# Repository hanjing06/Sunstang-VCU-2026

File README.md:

# Sunstang VCU 2026  
Vehicle Control Unit PCB for Western Sunstang

---

## Overview

The **Sunstang VCU 2026** is a custom-designed Vehicle Control Unit PCB developed in **KiCad v6+**.

The board integrates driver inputs, high-voltage enable logic, lighting control, safety interlocks, and vehicle state management into a centralized low-voltage control system.

The system is built around the **STM32 Nucleo-F302R8** development board (ARM Cortex-M4, 3.3V logic).

This PCB acts as the hardware interface between the microcontroller and the vehicle’s 12V automotive systems.

---

## System Architecture

The VCU operates across two voltage domains:

| Domain | Voltage | Description |
|--------|---------|-------------|
| Logic Domain | 3.3V | STM32 microcontroller logic |
| Automotive LV Domain | 12V | Switches, contactors, lighting, HV control |

Signal conditioning ensures safe interfacing between 12V automotive signals and 3.3V MCU GPIO/ADC inputs.

---

### System Integration Diagram

The diagram below shows the high-level integration of:

- STM32 Nucleo-F302R8 (3.3V logic domain)
- 12V automotive domain subsystems
- Pre-charge & contactor control
- Driver interface
- Lighting systems
- BMS interface

---

## Microcontroller

**Board:** STM32 Nucleo-F302R8  
**Core:** ARM Cortex-M4  
**Logic Voltage:** 3.3V  

Primary functions:
- ADC acquisition (accelerator and brake pedals)
- Digital input processing (switches and selectors)
- Digital output control (contactors, LEDs, lighting)
- Vehicle state logic (ready mode, charge mode, HV enable)

Documentation:  
https://www.st.com/en/evaluation-tools/nucleo-f302r8.html

---

## Functional Responsibilities

The VCU manages the following subsystems:

### 1. Power & HV Control
- LV switch interface (12V)
- HV switch interface (12V)
- Pre-charge button input
- Pre-charge contactor feedback
- Main contactor feedback
- HV active indication
- BMS interface signals

### 2. Driver Inputs
- Accelerator pedal (ADC input)
- Brake pedal (ADC/digital input)
- Brake light trigger output

### 3. Mode Control
- Ready mode switch
- Charge mode switch
- Mode select (SPDT)
- Gear selector (SPST)

### 4. Lighting Control
- Brake lights
- Daytime running lights (DRL)
- Left turn signal
- Right turn signal
- Hazard (latching)
- Rear signal outputs

### 5. Safety Inputs
- HV active confirmation
- Thermal shutdown input (redundancy planned)
- Pre-charge verification before main contactor closure

---

## Startup Sequence (Simplified)

1. LV switch enabled  
2. HV switch engaged  
3. Pre-charge initiated  
4. Pre-charge confirmed  
5. Main contactor closed  
6. HV active verified  
7. Ready mode enabled  
8. Vehicle operational  

---

## Electrical Characteristics

| Parameter | Value |
|------------|--------|
| Automotive LV Input | 12V DC |
| MCU Logic Voltage | 3.3V |
| Microcontroller | STM32F302R8 |
| Design Tool | KiCad v6+ |

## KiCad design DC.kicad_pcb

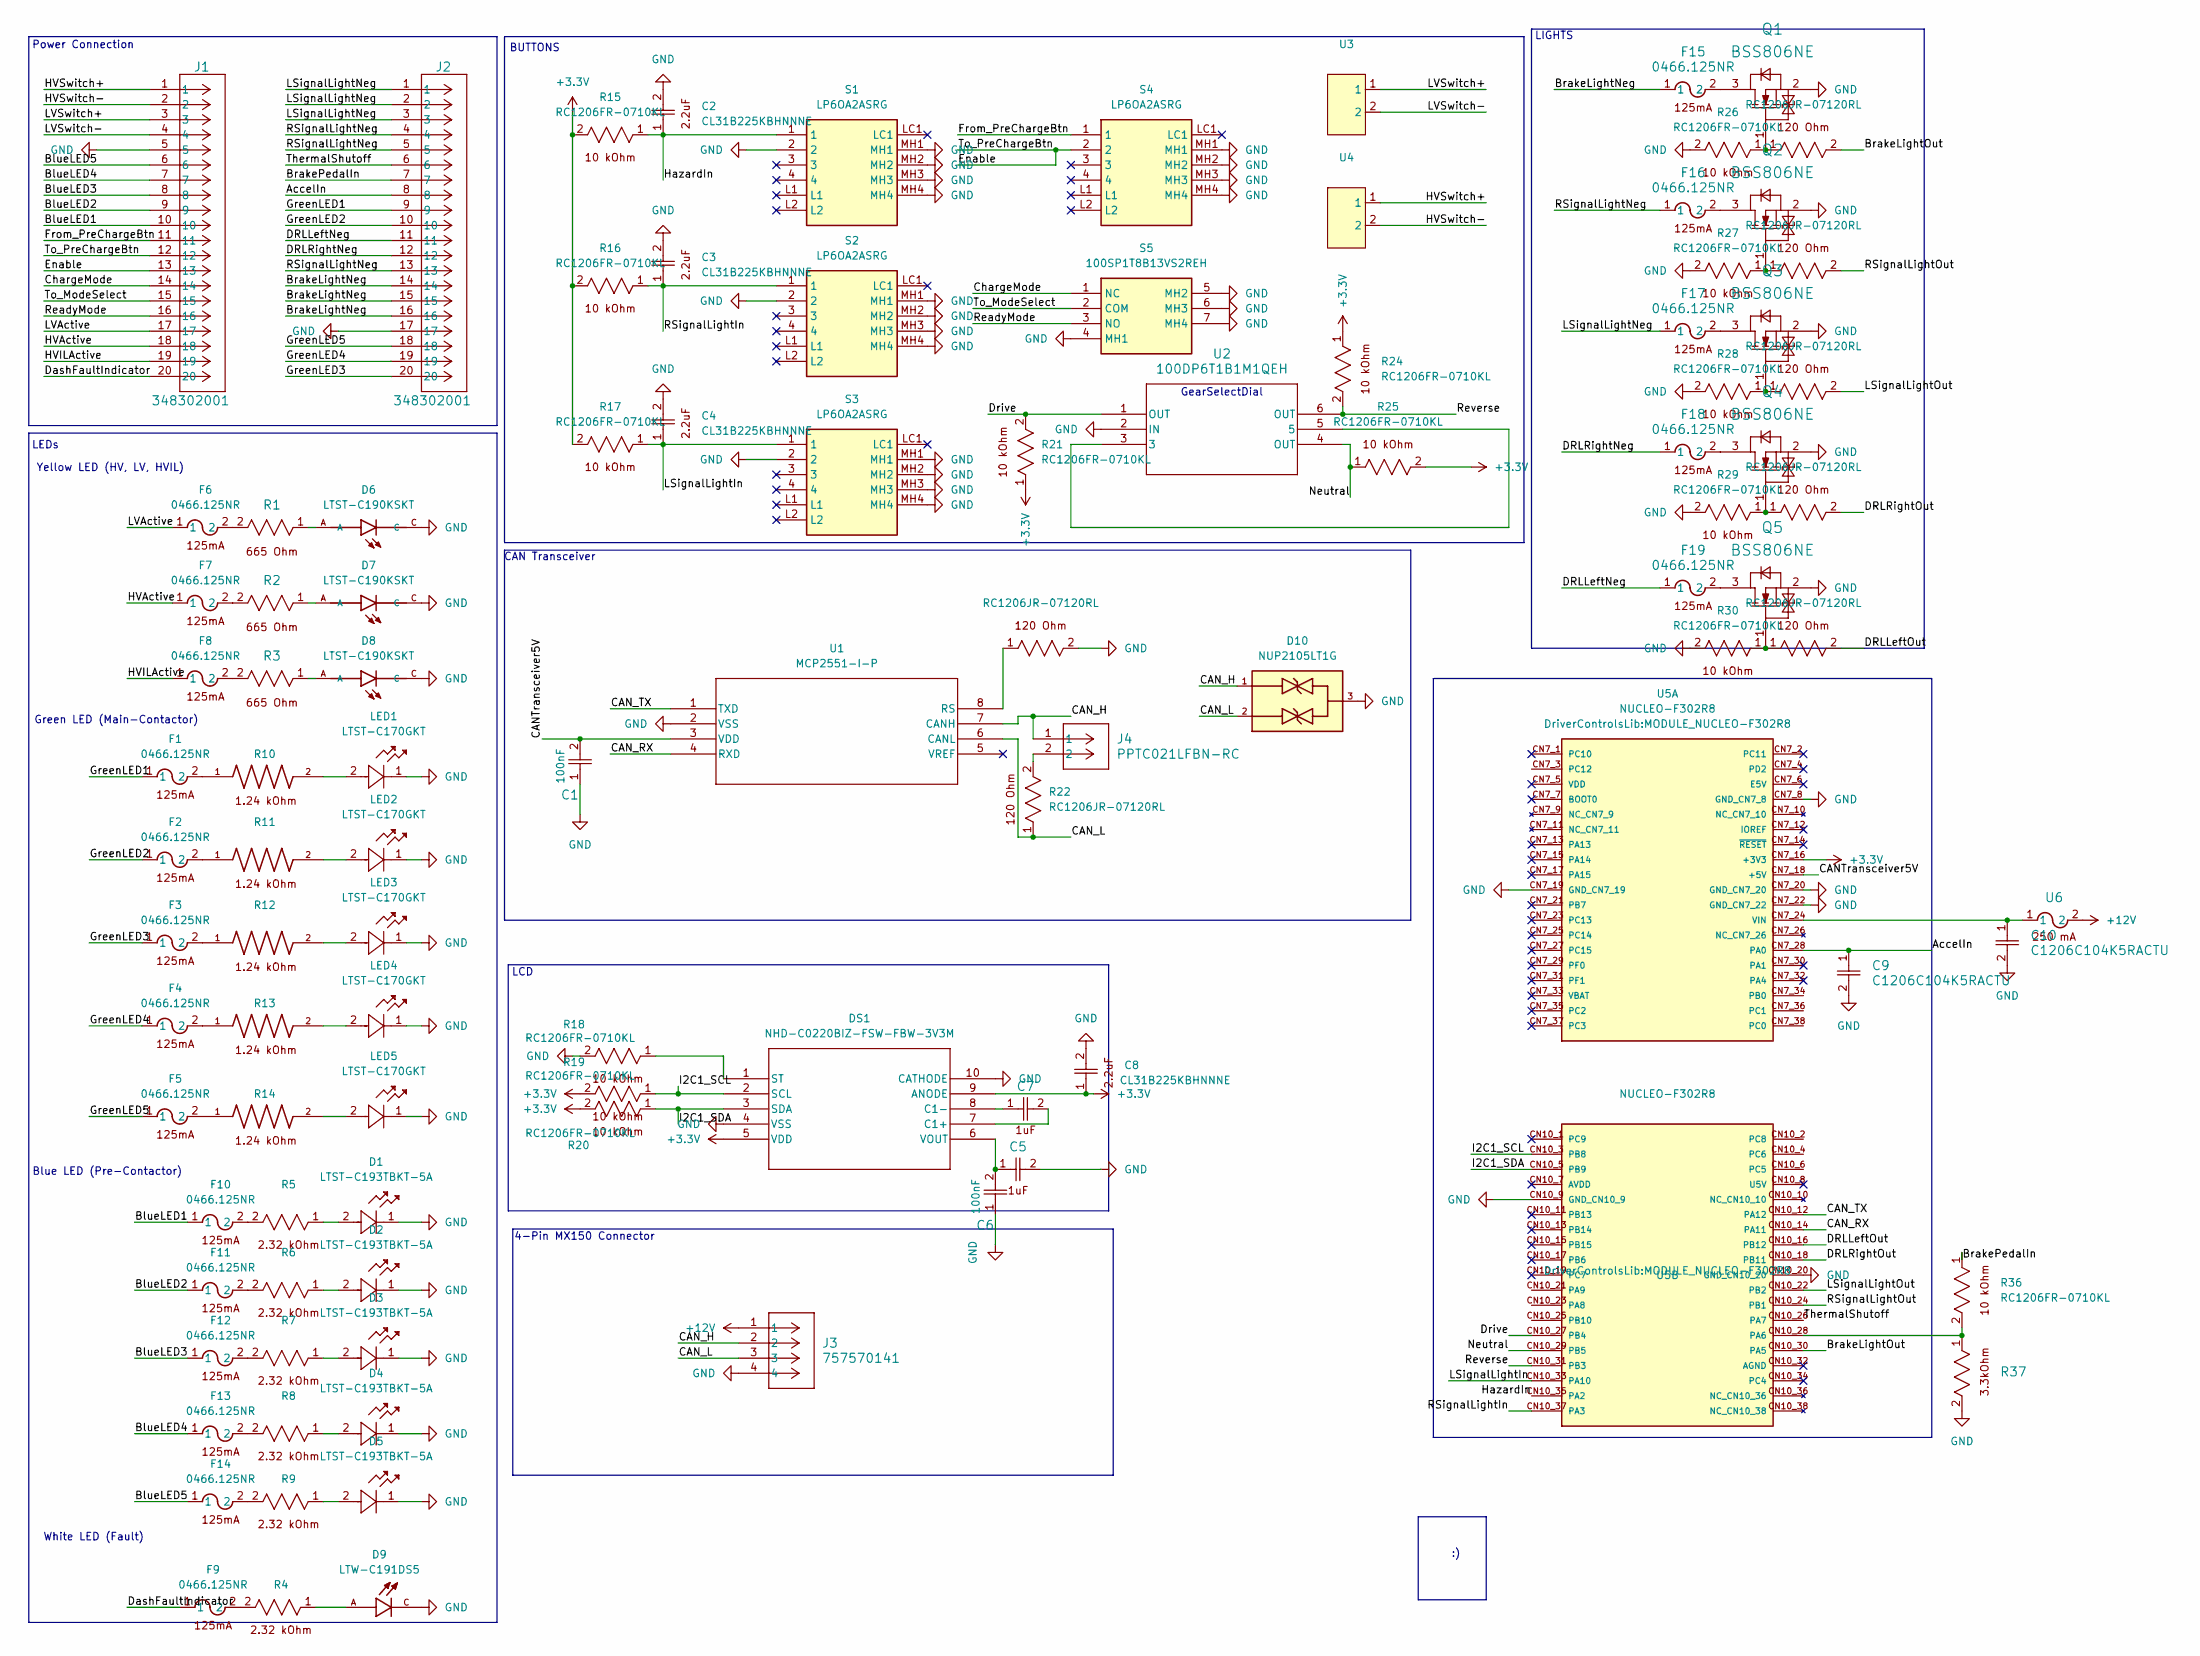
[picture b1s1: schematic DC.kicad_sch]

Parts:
C1, C6, C9, C10: C1206C104K5RACTU; CAPC340180_88N_KEM
C2, C3, C4, C8: CL31B225KBHNNNE; CAP_CL31_SAM
C5, C7: CL31B105KAHNNNE; CAP_CL31_SAM
D1, D2, D3, D4, D5: LTST-C193TBKT-5A; LED_LTST-C_LTO
D6, D7, D8: LTST-C190KSKT; LEDM1608X80
D9: LTW-C191DS5; LEDC1608X65N
D10: NUP2105LT1G; SOT95P237X111-3N; PARTREV 10
DS1: NHD-C0220BIZ-FSW-FBW-3V3M; NHD-C0220BIZ-FSW-FBW-3V3M_NDI; PARTREV 1.0
F1, F2, F3, F4, F5, F6, F7, F8, F9, F10, F11, F12, F13, F14: 0466.125NR; 0466Series_LTF; Mouser Part Number 576-0466.125NR
F15, F16, F17, F18, F19: 0466.125NR; 0466Series_LTF
J1, J2: 348302001; CONN_SD-34829-001_20_ST_MOL
J3: 757570141; CONN_SD-75757-010_1X4_F11p20_MOL
J4: PPTC021LFBN-RC; CONN2_LFBN-RC_SUL
LED1, LED2, LED3, LED4, LED5: LTST-C170GKT; LED_LTST-C170GKT_LTO
Q1, Q2, Q3, Q4, Q5: BSS806NE; SOT95P240X110-3N-1-V1
R1, R2, R3: RC1206FR-07665RL; RC1206N_YAG
R4, R5, R6, R7, R8, R9: RC1206FR-072K32L; RC1206N_YAG
R10, R11, R12, R13, R14: RC1206FR-071K24L; RESC3116X65N
R15, R16, R17, R18, R19, R20, R21, R24, R25, R26, R27, R28, R29, R30, R36: RC1206FR-0710KL; RC1206N_YAG
R22, R23, R31, R32, R33, R34, R35: RC1206JR-07120RL; RC1206N_YAG
R37: RC1206FR-073K3L; RC1206N_YAG
S1, S2, S3, S4: LP6OA2ASRG; Mouser Part Number 612-LP6OA2ASRG
S5: 100SP1T8B13VS2REH; Manufacturer_Part_Number 100SP1T8B13VS2REH
U1: MCP2551-I-P; PDIP8_300MC_MCH
U2: 100DP6T1B1M1QEH; TO_1M1QEH_EWI
U3: LV_Switch
U4: HV_Switch
U5: NUCLEO-F302R8; MODULE_NUCLEO-F302R8; PARTREV 17
U6: C1F 250; C1_BEL

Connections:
+3.3V: C8.1, DS1.5 (VDD), DS1.9 (ANODE), R15.2, R16.2, R17.2, R19.2, R20.2, R21.1, R24.1, R25.2, U5.CN7_16 (+3V3); also elsewhere on the board
+12V: J3.1, U6.2
/AccelIn: C9.1, J2.8, U5.CN7_28 (PA0)
/BlueLED1: F10.1, J1.10
/BlueLED2: F11.1, J1.9
/BlueLED3: F12.1, J1.8
/BlueLED4: F13.1, J1.7
/BlueLED5: F14.1, J1.6
/BrakeLightNeg: F15.1, J2.14, J2.15, J2.16
/BrakeLightOut: R31.2, U5.CN10_30 (PA5)
/BrakePedalIn: J2.7, R36.1
/CANTransceiver5V: C1.2, U1.3 (VDD), U5.CN7_18 (+5V)
/CAN_H: D10.1, J3.2, J4.1, U1.7 (CANH)
/CAN_L: D10.2, J3.3, R22.1, U1.6 (CANL)
/CAN_RX: U1.4 (RXD), U5.CN10_14 (PA11)
/CAN_TX: U1.1 (TXD), U5.CN10_12 (PA12)
/ChargeMode: J1.14, S5.1 (NC)
/DRLLeftNeg: F19.1, J2.11
/DRLLeftOut: R35.2, U5.CN10_16 (PB12)
/DRLRightNeg: F18.1, J2.12
/DRLRightOut: R34.2, U5.CN10_18 (PB11)
/DashFaultIndicator: F9.1, J1.20
/Drive: R21.2, U2.1 (OUT), U5.CN10_27 (PB4)
/Enable: J1.12, J1.13, S4.2
/From_PreChargeBtn: J1.11, S4.1
/GreenLED1: F1.1, J2.9
/GreenLED2: F2.1, J2.10
/GreenLED3: F3.1, J2.20
/GreenLED4: F4.1, J2.19
/GreenLED5: F5.1, J2.18
/HVActive: F7.1, J1.18
/HVILActive: F8.1, J1.19
/HVSwitch+: J1.1, U4.1
/HVSwitch-: J1.2, U4.2
/HazardIn: C2.1, R15.1, S1.1, U5.CN10_35 (PA2)
/I2C1_SCL: DS1.2 (SCL), R19.1, U5.CN10_3 (PB8)
/I2C1_SDA: DS1.3 (SDA), R20.1, U5.CN10_5 (PB9)
/LSignalLightIn: C4.1, R17.1, S3.1, U5.CN10_33 (PA10)
/LSignalLightNeg: F17.1, J2.1, J2.2, J2.3
/LSignalLightOut: R33.2, U5.CN10_22 (PB2)
/LVActive: F6.1, J1.17
/LVSwitch+: J1.3, U3.1
/LVSwitch-: J1.4, U3.2
/Neutral: R25.1, U2.4 (OUT), U5.CN10_29 (PB5)
/RSignalLightIn: C3.1, R16.1, S2.1, U5.CN10_37 (PA3)
/RSignalLightNeg: F16.1, J2.4, J2.5, J2.13
/RSignalLightOut: R32.2, U5.CN10_24 (PB1)
/ReadyMode: J1.16, S5.3 (NO)
/Reverse: R24.2, U2.6 (OUT), U5.CN10_31 (PB3)
/ThermalShutoff: J2.6, U5.CN10_26 (PA7)
/To_ModeSelect: J1.15, S5.2 (COM)
GND: C1.1, C2.2, C3.2, C4.2, C5.2, C6.1, C8.2, C9.2, C10.2, D1.1, D2.1, D3.1, D4.1, D5.1, D6.C, D7.C, D8.C, D9.C, D10.3, DS1.4 (VSS), DS1.10 (CATHODE), J1.5, J2.17, J3.4, LED1.1, LED2.1, LED3.1, LED4.1, LED5.1, Q1.2 (SOURCE), Q2.2 (SOURCE), Q3.2 (SOURCE), Q4.2 (SOURCE), Q5.2 (SOURCE), R18.2, R23.2, R26.2, R27.2, R28.2, R29.2, R30.2, R37.2, S1.2, S1.MH1, S1.MH2, S1.MH3, S1.MH4, S2.2, S2.MH1, S2.MH2, S2.MH3, S2.MH4, S3.2, S3.MH1, S3.MH2, S3.MH3, S3.MH4, S4.MH1, S4.MH2, S4.MH3, S4.MH4, S5.4 (MH1), S5.5 (MH2), S5.6 (MH3), S5.7 (MH4), U1.2 (VSS), U2.2 (IN), U5.CN7_8 (GND_CN7_8), U5.CN7_19 (GND_CN7_19), U5.CN7_20 (GND_CN7_20), U5.CN7_22 (GND_CN7_22), U5.CN10_9 (GND_CN10_9), U5.CN10_20 (GND_CN10_20); also elsewhere on the board
unnamed: D1.2, R5.1
unnamed: D2.2, R6.1
unnamed: D3.2, R7.1
unnamed: D4.2, R8.1
unnamed: D5.2, R9.1
unnamed: D6.A, R1.1
unnamed: D7.A, R2.1
unnamed: D8.A, R3.1
unnamed: C7.2, DS1.7 (C1+)
unnamed: C7.1, DS1.8 (C1-)
unnamed: DS1.1 (ST), R18.1
unnamed: C5.1, C6.2, DS1.6 (VOUT)
unnamed: F1.2, R10.1
unnamed: F2.2, R11.1
unnamed: F3.2, R12.1
unnamed: F4.2, R13.1
unnamed: F5.2, R14.1
unnamed: F6.2, R1.2
unnamed: F7.2, R2.2
unnamed: F8.2, R3.2
unnamed: F10.2, R5.2
unnamed: F11.2, R6.2
unnamed: F12.2, R7.2
unnamed: F13.2, R8.2
unnamed: F14.2, R9.2
unnamed: J4.2, R22.2
unnamed: LED1.2, R10.2
unnamed: LED2.2, R11.2
unnamed: LED3.2, R12.2
unnamed: LED4.2, R13.2
unnamed: LED5.2, R14.2
unnamed: F15.2, Q1.3 (DRAIN)
unnamed: Q1.1 (GATE), R26.1, R31.1
unnamed: F16.2, Q2.3 (DRAIN)
unnamed: Q2.1 (GATE), R27.1, R32.1
unnamed: F17.2, Q3.3 (DRAIN)
unnamed: Q3.1 (GATE), R28.1, R33.1
unnamed: F18.2, Q4.3 (DRAIN)
unnamed: Q4.1 (GATE), R29.1, R34.1
unnamed: F19.2, Q5.3 (DRAIN)
unnamed: Q5.1 (GATE), R30.1, R35.1
unnamed: R23.1, U1.8 (RS)
unnamed: U2.3, U2.5
unnamed: C10.1, U5.CN7_24 (VIN), U6.1
unnamed: R36.2, R37.1, U5.CN10_28 (PA6)

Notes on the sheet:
Power Connection
CAN Transceiver
BUTTONS
White LED (Fault)
GearSelectDial
Blue LED (Pre-Contactor)
LIGHTS
Yellow LED (HV, LV, HVIL)
LCD
LEDs
4-Pin MX150 Connector
Green LED (Main-Contactor)

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
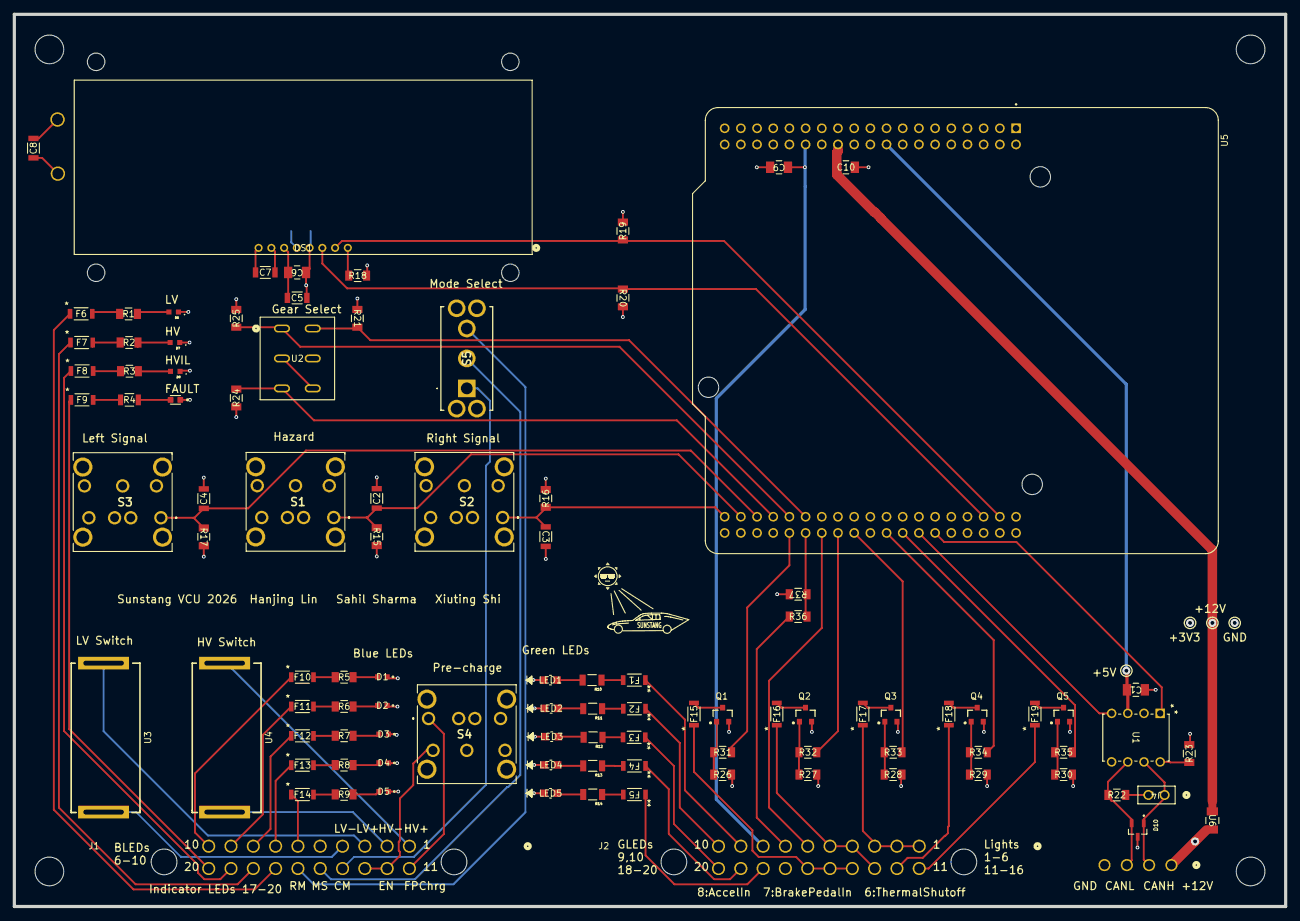
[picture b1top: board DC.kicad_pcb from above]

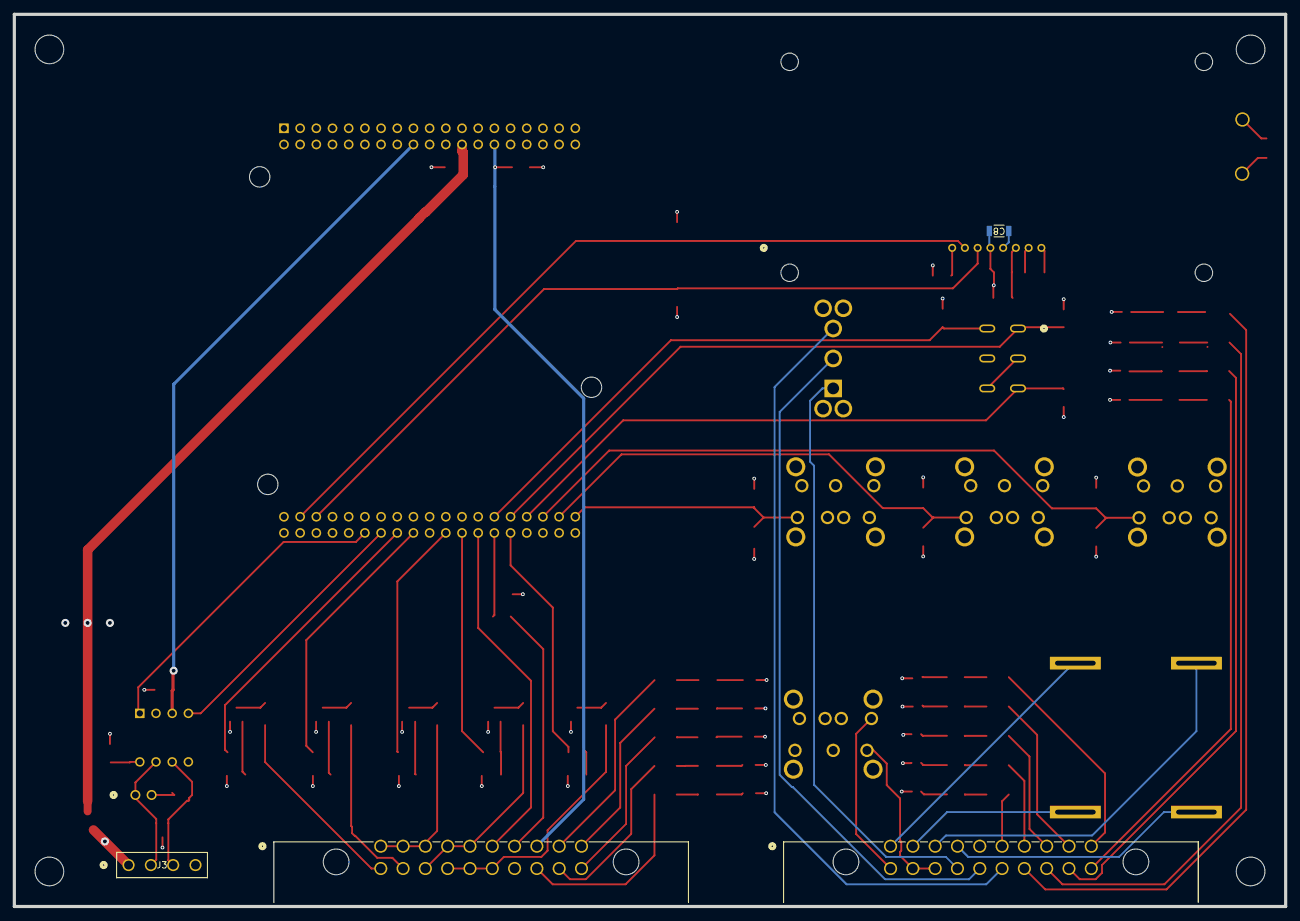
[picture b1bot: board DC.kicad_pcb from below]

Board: 4 copper layers, 199.5 x 140.0 mm, 103 parts (4 on the bottom side), 99 nets.

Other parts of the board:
C8#2: CL31B225KBHNNNE; CAP_CL31_SAM

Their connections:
+3.3V: C8#2.1; also elsewhere on the board
GND: C8#2.2; also elsewhere on the board

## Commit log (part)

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2026-02-11 Updated LEDs, buttons and power distribution headers
2026-02-11 Imported footprints
2026-02-11 AccelIn to adc and I2C connection
2026-02-11 Deleted buttons!
2026-02-11 Added LCD!
2026-02-11 Symbols all have a footprint and LCD added
2026-02-13 Fixed airwires and CANtransceiver, added mode select switch
2026-02-13 LEDs routed
2026-02-13 Added HV and LV switches
2026-02-16 Routed front and back
2026-02-16 Updated symbols/footprints
2026-02-16 Change molex orientation
2026-02-16 3v3 power
2026-02-18 Added gear-select, needs to be wired
2026-02-19 Updated pcb with new routing and gear select. Still errors to correct
2026-02-21 VCU revisions, last review still to be done
2026-02-23 small corrections, added voltage divider for BreakPedalIn
2026-02-25 Systems png
2026-02-25 project details
2026-02-25 Update README by removing repository structure section
    Removed repository structure section from README.
2026-02-25 Fix image source path for VCU system diagram
    Updated image source path in README.
